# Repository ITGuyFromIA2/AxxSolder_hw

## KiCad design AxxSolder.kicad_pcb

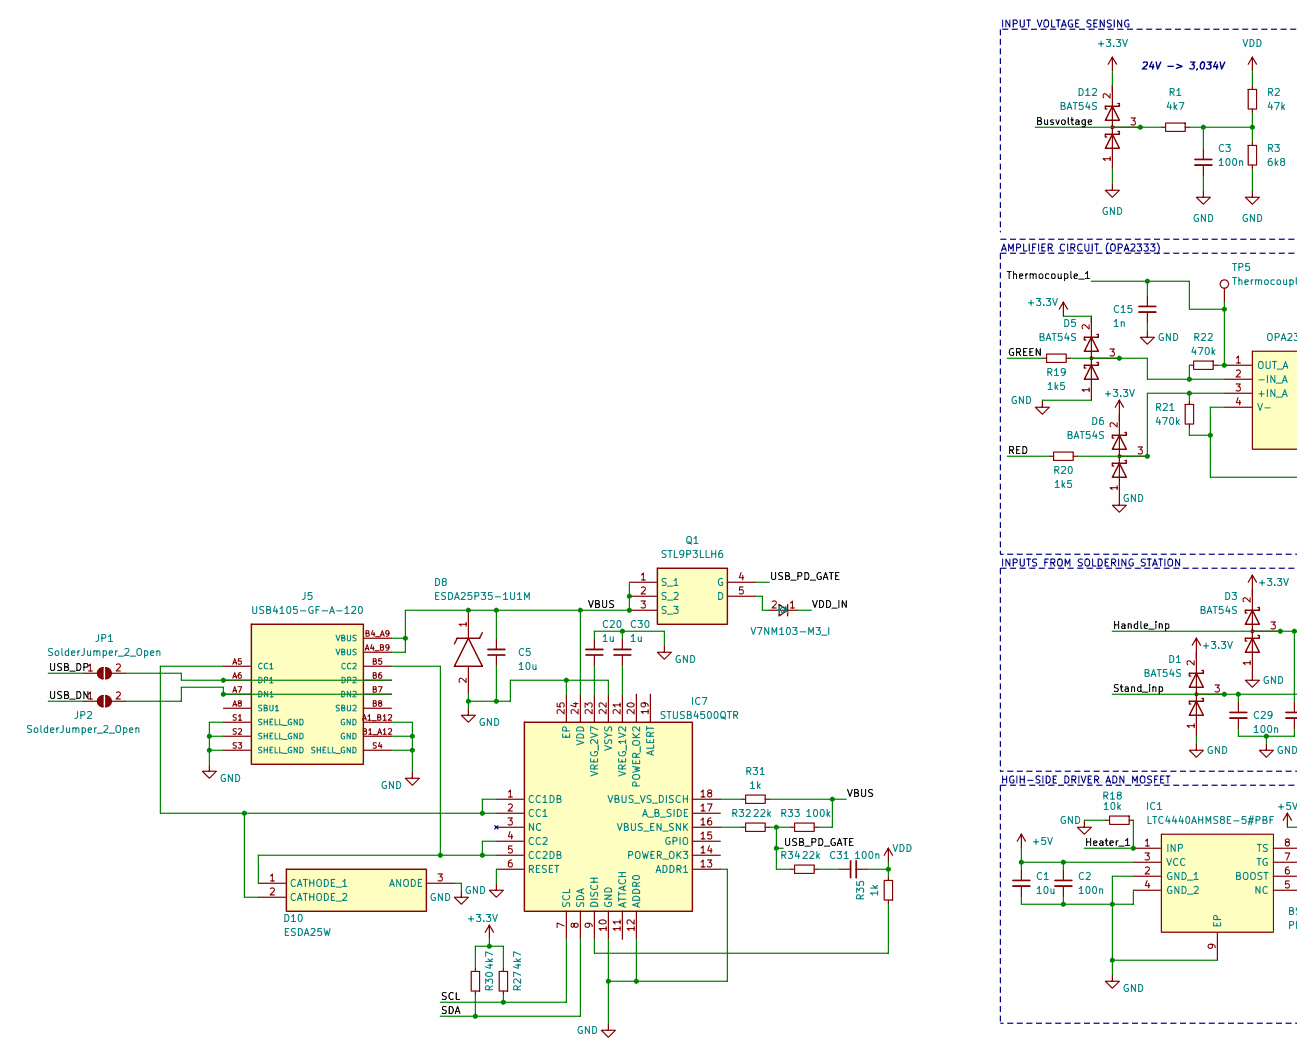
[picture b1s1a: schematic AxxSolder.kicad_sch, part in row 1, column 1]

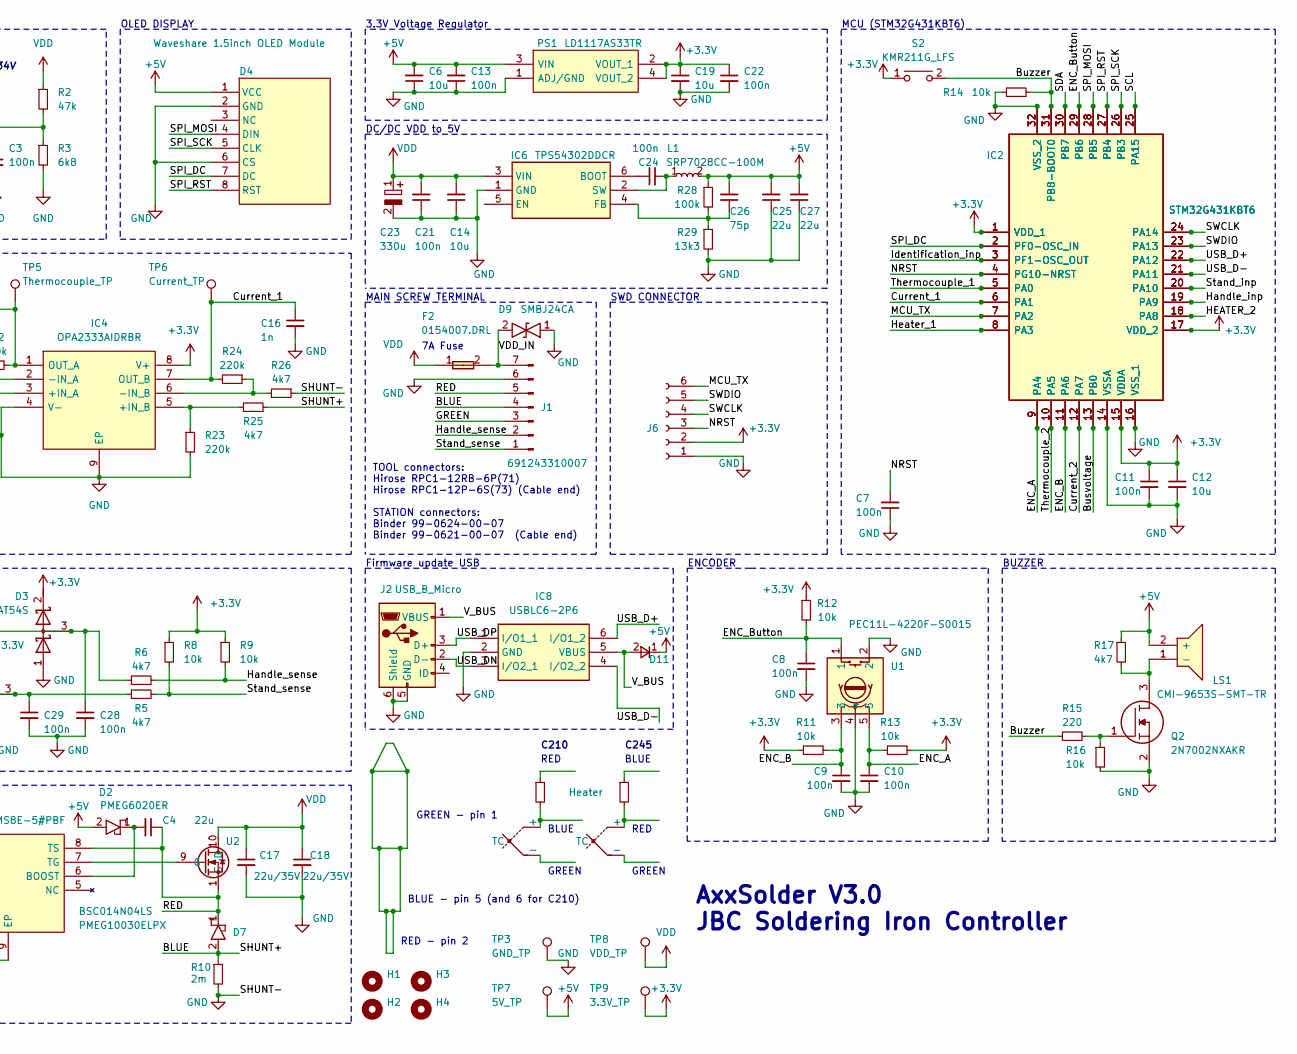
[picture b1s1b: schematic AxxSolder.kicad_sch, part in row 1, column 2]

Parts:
C1, C5, C6, C12, C14, C19: 10u; C_0805_2012Metric; Manufacturer_Part_Number GRM21BR6YA106ME43L
C2, C3, C7, C8, C9, C10, C11, C13, C21, C22, C24, C28, C29, C31: 100n; C_0805_2012Metric; Manufacturer_Part_Number GRM21BR72A104KAC4L
C4, C25, C27: 22u; C_1206_3216Metric; Manufacturer_Part_Number C2012X6S1C226M125AC
C15, C16: 1n; C_0805_2012Metric; Manufacturer_Part_Number GRM2165C1H102JA01D
C17, C18: 22u/35V; C_1206_3216Metric; Manufacturer_Part_Number C3216X5R1V226M160AC
C20, C30: 1u; C_0805_2012Metric; Manufacturer_Part_Number GRM21BC72A105KE01L
C23: 330u; CAPAE1030X1050N; Mouser Part Number 661-EMZR500ARA331MJA
C26: 75p; C_0805_2012Metric; Manufacturer_Part_Number GRM21A5C2E750FW01D
D1, D3, D5, D6, D12: BAT54S; SOT95P230X110-3N; Manufacturer_Part_Number BAT54S
D2: PMEG6020ER; PMEG6020ER115; Mouser Part Number 771-PMEG6020ER-115
D4: Waveshare 1.5inch OLED Module; 1_5inch-rgb-oled-module_asm-1110; Manufacturer_Part_Number N/A
D7: PMEG10030ELPX; SODFL4725X110N; Mouser Part Number 771-PMEG10030ELPX
D8: ESDA25P35-1U1M; ESDA25P351U1M; Mouser Part Number 511-ESDA25P35-1U1M
D9: SMBJ24CA; DIOM5436X261N; Mouser Part Number 576-SMBJ24CA
D10: ESDA25W; SOT65P210X110-3N; Mouser Part Number 511-ESDA25W
D11: 1N5819HW-7-F; SOD3716X145N; Mouser Part Number 621-1N5819HW-F
D13: V7NM103-M3_I; V7NM103M3I; Mouser Part Number 625-V7NM103-M3/I
F2: 0154007.DRL; 0154100DR; Mouser Part Number 576-0154007.DRL
H1, H2, H3, H4: MountingHole; MountingHole_3mm
IC1: LTC4440AHMS8E-5#PBF; SOP65P490X110-9N; Mouser Part Number 584-C4440AHMS8E-5PBF
IC2: STM32G431KBT6; QFP80P900X900X160-32N; Mouser Part Number 511-STM32G431KBT6
IC4: OPA2333AIDRBR; SON65P300X300X100-9N-D; Mouser Part Number 595-OPA2333AIDRBR
IC5: STM32G431KBT6; UFQFPN-32-1EP_5x5mm_P0.5mm_EP3.5x3.5mm; Mouser Part Number 511-STM32G431KBT6
IC6: TPS54302DDCR; SOT95P280X110-6N; Mouser Part Number 595-TPS54302DDCR
IC7: STUSB4500QTR; QFN50P400X400X100-25N-D; Mouser Part Number 511-STUSB4500QTR
IC8: USBLC6-2P6; USBLC62P6; Mouser Part Number 511-USBLC6-2P6
J1: Conn_01x07_Male; 691243310007; Manufacturer_Part_Number 691243310007
J2: USB_B_Micro; GCT_USB3140-30-0230-1-C_REVE1; Manufacturer_Part_Number USB3140-30-0170-0-C
J5: USB4105-GF-A-120; GCT_USB4105-GF-A-120; PARTREV A3
J6: Conn_01x06_Socket; PinSocket_1x06_P2.54mm_Vertical; Manufacturer_Part_Number 61300611821
JP1, JP2: SolderJumper_2_Open; SolderJumper-2_P1.3mm_Open_TrianglePad1.0x1.5mm
L1: SRP7028CC-100M; INDPM7366X300N; Manufacturer_Part_Number SRP7028CC-100M
LS1: CMI-9653S-SMT-TR; CMI9653SSMTTR; Mouser Part Number 490-CMI-9653S-SMT-TR
PS1: LD1117AS33TR; SOT230P700X190-4N; Mouser Part Number 511-LD1117AS33
Q1: STL9P3LLH6; STL20N6F7; Mouser Part Number 511-STL9P3LLH6
Q2: 2N7002NXAKR; SOT95P230X110-3N; Manufacturer_Part_Number 2N7002NXAKR; Mouser Part Number 771-2N7002NXAKR
R1, R5, R6, R17, R25, R26, R27, R30: 4k7; R_0805_2012Metric; Manufacturer_Part_Number ERJ-6ENF4701V
R2: 47k; R_0805_2012Metric; Manufacturer_Part_Number ERJ-6ENF4702V
R3: 6k8; R_0805_2012Metric; Manufacturer_Part_Number ERJ-6ENF6801V
R4: Heater
R7: Heater 2 OHM
R8, R9, R11, R12, R13, R14, R16, R18: 10k; R_0805_2012Metric; Manufacturer_Part_Number ERJ-6ENF1002V
R10: 2m; RESC6432X89N; part_id WSLP25122L500FEA
R15: 220; R_0805_2012Metric; Manufacturer_Part_Number ERJ-6ENF2200V
R19, R20: 1k5; R_0805_2012Metric; Manufacturer_Part_Number ERJ-6ENF1501V
R21, R22: 470k; R_0805_2012Metric; Manufacturer_Part_Number ERJ-6ENF4703V
R23, R24: 220k; R_0805_2012Metric; Manufacturer_Part_Number ERJ-6ENF2203V
R28, R33: 100k; R_0805_2012Metric; Manufacturer_Part_Number ERJ-6ENF1003V
R29: 13k3; R_0805_2012Metric; Manufacturer_Part_Number ERJ-6ENF1332V
R31, R35: 1k; R_0805_2012Metric; Manufacturer_Part_Number ERJ-6ENF1001V
R32, R34: 22k; R_0805_2012Metric; Manufacturer_Part_Number ERJ-6ENF2202V
S2: KMR211G_LFS; KMR_2; Manufacturer_Part_Number KMR211G LFS; Mouser Part Number 611-KMR211G-LFS
TC1, TC2: TC
TP3: GND_TP; TestPoint_THTPad_D1.0mm_Drill0.5mm
TP5: Thermocouple_TP; TestPoint_Pad_D1.0mm
TP6: Current_TP; TestPoint_Pad_D1.0mm
TP7: 5V_TP; TestPoint_THTPad_D1.0mm_Drill0.5mm
TP8: VDD_TP; TestPoint_THTPad_D1.0mm_Drill0.5mm
TP9: 3.3V_TP; TestPoint_THTPad_D1.0mm_Drill0.5mm
U1: PEC11L-4220F-S0015; PEC11L4220FS0015; Mouser Part Number 652-PEC11L4220FS0015
U2: BSC014N04LS; Manufacturer_Part_Number BSC014N04LSATMA1

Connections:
+3.3V: C11.1, C12.1, C19.1, C22.1, D1.2 (K), D3.2 (K), D5.2 (K), D6.2 (K), D12.2 (K), IC2.1 (VDD_1), IC2.15 (VDDA), IC2.17 (VDD_2), IC4.8 (V+), IC5.1 (VDD_1), IC5.15 (VDDA), IC5.17 (VDD_2), J6.2, PS1.2 (VOUT_1), PS1.4 (VOUT_2), R8.1, R9.1, R11.2, R12.1, R13.1, R27.2, R30.2, S2.1, TP9.1
+5V: C1.1, C2.1, C6.2, C13.2, C25.2, C26.2, C27.2, D2.2, D4.1 (VCC), D11.1, IC1.3 (VCC), L1.2, LS1.2 (+), PS1.3 (VIN), R17.1, R28.1, TP7.1
/BLUE: D7.2, J1.4, R10.1, R25.2
/Busvoltage: D12.3 (common), IC2.13 (PB0), IC5.13 (PB0), R1.2
/Buzzer: IC2.31 (PB8-BOOT0), IC5.31 (PB8-BOOT0), R14.2, R15.1, S2.2
/Current_1: C16.1, IC2.6 (PA1), IC4.7 (OUT_B), IC5.6 (PA1), R24.2, TP6.1; also elsewhere on the board
/Current_2: IC2.12 (PA7), IC5.12 (PA7)
/ENC_A: C10.1, IC2.9 (PA4), IC5.9 (PA4), R13.2, U1.5
/ENC_B: C9.1, IC2.11 (PA6), IC5.11 (PA6), R11.1, U1.3
/ENC_Button: C8.1, IC2.29 (PB6), IC5.29 (PB6), R12.2, U1.1
/GREEN: J1.3, R19.1
/HEATER_2: IC2.18 (PA8), IC5.18 (PA8)
/Handle_inp: C28.1, D3.3 (common), IC2.19 (PA9), IC5.19 (PA9), R6.1
/Handle_sense: J1.2, R6.2, R9.2
/Heater_1: IC1.1 (INP), IC2.8 (PA3), IC5.8 (PA3), R18.1
/Identification_inp: IC2.3 (PF1-OSC_OUT), IC5.3 (PF1-OSC_OUT)
/MCU_TX: IC2.7 (PA2), IC5.7 (PA2), J6.6
/NRST: C7.2, IC2.4 (PG10-NRST), IC5.4 (PG10-NRST), J6.3
/RED: C4.1, D7.1, IC1.8 (TS), J1.5, R20.1, U2.1 (S)
/SCL: IC2.25 (PA15), IC5.25 (PA15), IC7.7 (SCL), R27.1
/SDA: IC2.30 (PB7), IC5.30 (PB7), IC7.8 (SDA), R30.1
/SPI_DC: D4.7 (DC), IC2.2 (PF0-OSC_IN), IC5.2 (PF0-OSC_IN)
/SPI_MOSI: D4.4 (DIN), IC2.28 (PB5), IC5.28 (PB5)
/SPI_RST: D4.8 (RST), IC2.27 (PB4), IC5.27 (PB4)
/SPI_SCK: D4.5 (CLK), IC2.26 (PB3), IC5.26 (PB3)
/SWCLK: IC2.24 (PA14), IC5.24 (PA14), J6.4
/SWDIO: IC2.23 (PA13), IC5.23 (PA13), J6.5
/Stand_inp: C29.1, D1.3 (common), IC2.20 (PA10), IC5.20 (PA10), R5.1
/Stand_sense: J1.1, R5.2, R8.2
/Thermocouple_1: C15.1, IC2.5 (PA0), IC4.1 (OUT_A), IC5.5 (PA0), R22.1, TP5.1; also elsewhere on the board
/Thermocouple_2: IC2.10 (PA5), IC5.10 (PA5)
/USB_D+: IC2.22 (PA12), IC5.22 (PA12), IC8.6 (I/O1_2)
/USB_D-: IC2.21 (PA11), IC5.21 (PA11), IC8.4 (I/O2_2)
/USB_DN: IC8.3 (I/O2_1), J2.2 (D-), JP2.1 (A)
/USB_DP: IC8.1 (I/O1_1), J2.3 (D+), JP1.1 (A)
/USB_PD_GATE: Q1.4 (G), R32.2, R33.1, R34.1
/VBUS: C5.2, D8.1 (K), IC7.24 (VDD), J5.A4_B9 (VBUS), J5.B4_A9 (VBUS), Q1.1 (S_1), Q1.2 (S_2), Q1.3 (S_3), R31.2, R33.2
/VDD_IN: D9.2, D13.1 (K), F2.2, J1.7
/V_BUS: D11.2, IC8.5 (VBUS), J2.1 (VBUS)
GND: C1.2, C2.2, C3.2, C5.1, C6.1, C7.1, C8.2, C9.2, C10.2, C11.2, C12.2, C13.1, C14.1, C15.2, C16.2, C17.2, C18.2, C19.2, C20.2, C21.1, C22.2, C23.2, C25.1, C27.1, C28.2, C29.2, C30.2, D1.1 (A), D3.1 (A), D4.2 (GND), D4.6 (CS), D5.1 (A), D6.1 (A), D8.2 (A), D9.1, D10.3 (ANODE), D12.1 (A), IC1.2 (GND_1), IC1.4 (GND_2), IC1.9 (EP), IC2.14 (VSSA), IC2.16 (VSS_1), IC2.32 (VSS_2), IC4.4 (V-), IC4.9 (EP), IC5.14 (VSSA), IC5.16 (VSS_1), IC5.32 (VSS_2), IC6.1 (GND), IC7.6 (RESET), IC7.10 (GND), IC7.12 (ADDR0), IC7.13 (ADDR1), IC7.22 (VSYS), IC7.25 (EP), IC8.2 (GND), J1.6, J2.5 (GND), J2.6 (Shield), J5.A1_B12 (GND), J5.B1_A12 (GND), J5.S1 (SHELL_GND), J5.S2 (SHELL_GND), J5.S3 (SHELL_GND), J5.S4 (SHELL_GND), J6.1, PS1.1 (ADJ/GND), Q2.2, R3.2, R10.2, R14.1, R16.2, R18.2, R21.2, R23.2, R26.1, R29.2, TP3.1, U1.2, U1.4
unnamed: C3.1, R1.1, R2.2, R3.1
unnamed: C31.1, R34.2
unnamed: D5.3 (common), IC4.2 (-IN_A), R19.2, R22.2
unnamed: D6.3 (common), IC4.3 (+IN_A), R20.2, R21.1
unnamed: D10.1 (CATHODE_1), IC7.4 (CC2), IC7.5 (CC2DB), J5.B5 (CC2)
unnamed: D10.2 (CATHODE_2), IC7.1 (CC1DB), IC7.2 (CC1), J5.A5 (CC1)
unnamed: D13.2 (A), Q1.5 (D)
unnamed: C4.2, D2.1, IC1.6 (BOOST)
unnamed: IC1.7 (TG), U2.9 (G)
unnamed: IC4.5 (+IN_B), R23.1, R25.1
unnamed: IC4.6 (-IN_B), R24.1, R26.2
unnamed: C24.1, IC6.6 (BOOT)
unnamed: C26.1, IC6.4 (FB), R28.2, R29.1
unnamed: C24.2, IC6.2 (SW), L1.1
unnamed: IC7.9 (DISCH), R35.1
unnamed: IC7.16 (VBUS_EN_SNK), R32.1
unnamed: IC7.18 (VBUS_VS_DISCH), R31.1
unnamed: C30.1, IC7.21 (VREG_1V2)
unnamed: C20.1, IC7.23 (VREG_2V7)
unnamed: J5.A7 (DN1), J5.B7 (DN2), JP2.2 (B)
unnamed: J5.A6 (DP1), J5.B6 (DP2), JP1.2 (B)
unnamed: LS1.1 (-), Q2.3, R17.2
unnamed: Q2.1, R15.2, R16.1
unnamed: R4.2, TC1.1 (+)
unnamed: R7.2, TC2.1 (+)
VDD: C14.2, C17.1, C18.1, C21.2, C23.1, C31.2, F2.1, IC6.3 (VIN), R2.1, R35.2, TP8.1, U2.10 (D)

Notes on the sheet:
7A Fuse
C210
Firmware update USB
MCU (STM32G431KBT6)
C245
GREEN - pin 1
MAIN SCREW TERMINAL
AMPLIFIER CIRCUIT (OPA2333)
24V -> 3,034V
INPUT VOLTAGE SENSING
ENCODER
SWD CONNECTOR
BLUE
BLUE - pin 5 (and 6 for C210)
GREEN
RED
BUZZER
DC/DC VDD to 5V
AxxSolder V3.0 JBC Soldering Iron Controller
TOOL connectors: Hirose RPC1-12RB-6P(71) Hirose RPC1-12P-6S(73) (Cable end) STATION connectors: Binder 99-0624-00-07 Binder 99-0621-00-07 (Cable end)
INPUTS FROM SOLDERING STATION
HGIH-SIDE DRIVER ADN MOSFET
RED - pin 2
RED
3.3V Voltage Regulator
OLED DISPLAY

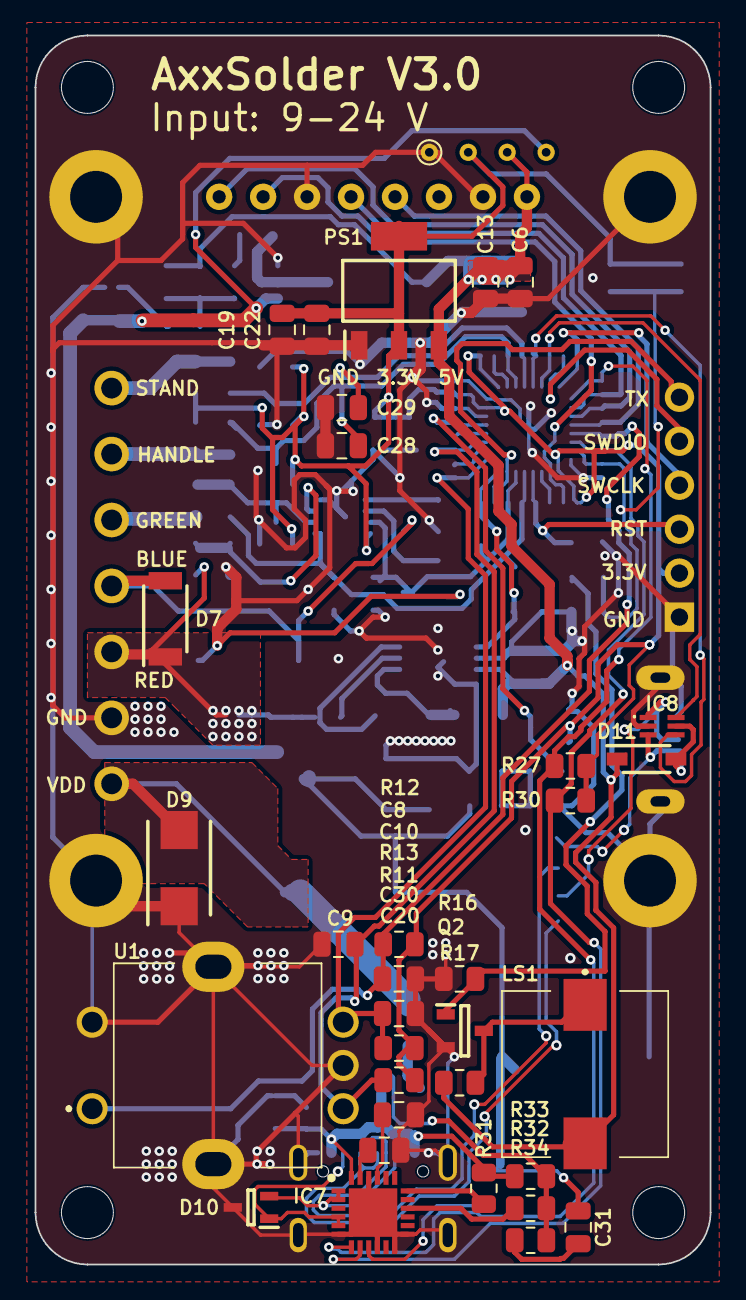
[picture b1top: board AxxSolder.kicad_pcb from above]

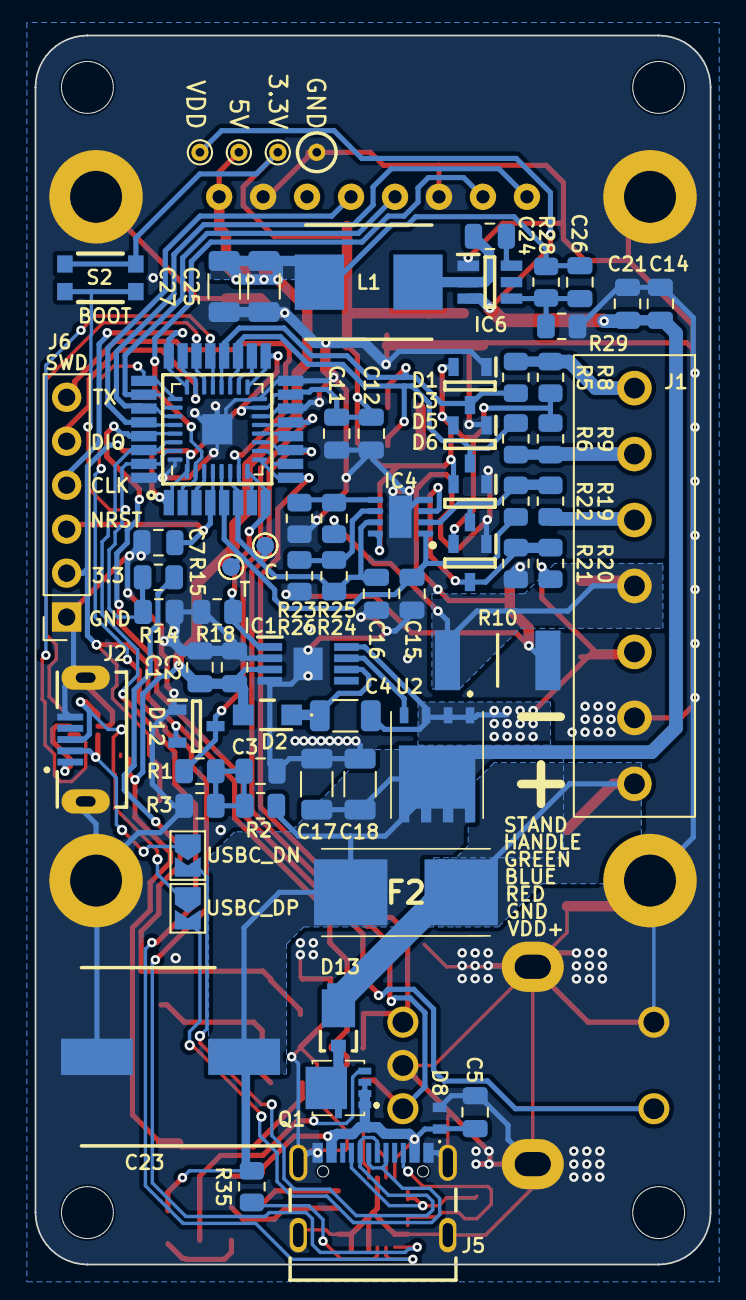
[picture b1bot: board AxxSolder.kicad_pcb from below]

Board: 2 copper layers, 39.0 x 71.0 mm, 111 parts (73 on the bottom side), 64 nets.

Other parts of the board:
TP5#2: Thermocouple_TP; TestPoint_Pad_D1.0mm
TP6#2: Current_TP; TestPoint_Pad_D1.0mm

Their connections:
/Current_1: TP6#2.1; also elsewhere on the board
/Thermocouple_1: TP5#2.1; also elsewhere on the board

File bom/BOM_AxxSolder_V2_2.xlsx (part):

AxxSolder V2.2 | Prises as per 2023-10-03 |  | Parts for AxxSolder Station only
 |  |  | Parts for AxxSolder Poratble only
Part | Value | Device | Footprint | # in design | Price / component | Price / unit |  |  | Datasheet | Manufacturer_Part_Number | Mouser Part Number
C1, C6, C12, C14, C19 | 10u | Device:C_Small | Capacitor_SMD:C_0805_2012Metric | 5 | 0.32 | 1.6 | https://www.mouser.se/ProductDetail/Murata-Electronics/GRM21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 | https://www.mouser.com/ProductDetail/Murata-Electronics/GRM2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 | ~
C2, C3, C5, C7, C8, C9, C10, C11, C13, C20, C21, C22, C24, C28, C29 | 100n | Device:C_Small | Capacitor_SMD:C_0805_2012Metric | 15 | 9.2999999999999999E-2 | 1.395 | https://www.mouser.se/ProductDetail/KYOCERA-AVX/KGM21NR71H10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 | https://www.mouser.com/ProductDetail/KYOCERA-AVX/KGM21NR71H1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 | ~
C4, C25, C27 | 22u | Device:C_Small | Capacitor_SMD:C_1206_3216Metric | 3 | 0.54 | 1.62 | https://www.mouser.se/ProductDetail/TDK/C2012X6S1C226M125AC?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 | https://www.mouser.com/ProductDetail/TDK/C2012X6S1C226M125AC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
C17, C18 | 22u/35V | Device:C_Small | Capacitor_SMD:C_0805_2012Metric | 2 | 0.88 | 1.76 | https://www.mouser.se/ProductDetail/TDK/C3216X5R1V226M160AC?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 | https://www.mouser.com/ProductDetail/TDK/C3216X5R1V226M160AC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
C15, C16 | 1n | Device:C_Small | Capacitor_SMD:C_0805_2012Metric | 2 | 9.2999999999999999E-2 | 0.186 | https://www.mouser.se/ProductDetail/KYOCERA-AVX/KGM21NR71H10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 | https://www.mouser.com/ProductDetail/KYOCERA-AVX/KGM21NR71H1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 | ~
C23 | 330u | EMZR500ARA331MJA0G:EMZR500ARA331MJA0G | EMZR500ARA331MJA0G:CAPAE1030X1050N | 1 | 1.1599999999999999 | 1.1599999999999999 | https://www.mouser.se/ProductDetail/Chemi-Con/EMZR500ARA331M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 | https://www.mouser.com/ProductDetail/Chemi-Con/EMZR500ARA331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 | https://ru.mouser.com/datasheet/2/420/United-Chemi-Con-776012.pdf | EMZR500ARA331MJA0G | 661-EMZR500ARA331MJA
C26 | 75p | Device:C_Small | Capacitor_SMD:C_0805_2012Metric | 1 | 0.15 | 0.15 | https://www.mouser.se/ProductDetail/KYOCERA-AVX/08051A750JAT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 | https://www.mouser.com/ProductDetail/KYOCERA-AVX/08051A750JA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 |  | 08051A750JAT2A
D1, D3, D5, D6, D12 | BAT54S | Device:D_Schottky_Dual_Series_AKC | BAT54S,215:SOT95P230X110-3N | 5 | 0.26 | 1.3 | https://www.mouser.se/ProductDetail/Diotec-Semiconductor/BAT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 | https://www.mouser.com/ProductDetail/Diotec-Semiconductor/BA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 | ~
D2 | PMEG6020ER | PMEG6020ER_115:PMEG6020ER,115 | PMEG6020ER,115:PMEG6020ER115 | 1 | 0.41899999999999998 | 0.41899999999999998 | https://www.mouser.se/ProductDetail/Nexperia/PMEG6020ER115?q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 | https://www.mouser.com/ProductDetail/Nexperia/PMEG6020ER115?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 | https://assets.nexperia.com/documents/data-sheet/PMEG6020ER.pdf | PMEG6020ER,115 | 771-PMEG6020ER-115
D4 | Waveshare 1.5inch OLED Module | 1_5inch-rgb-oled-module_asm-1110:1_5inch-rgb-oled-module_asm-1110 | 1_5inch-rgb-oled-module_asm-1110:1_5inch-rgb-oled-module_asm-1110 | 1 | 12.9 | 12.9 | https://www.welectron.com/Waveshare-13992-15inch-OLED-Module_1 | https://www.welectron.com/Waveshare-13992-15inch-OLED-Module_1
D7 | PMEG10030ELPX | PMEG10030ELPX:PMEG10030ELPX | PMEG10030ELPX:SODFL4725X110N | 1 | 0.44600000000000001 | 0.44600000000000001 | https://www.mouser.se/ProductDetail/Nexperia/PMEG10030ELPX?q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 | https://www.mouser.com/ProductDetail/Nexperia/PMEG10030ELPX?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 | https://assets.nexperia.com/documents/data-sheet/PMEG10030ELP.pdf | PMEG10030ELPX | 771-PMEG10030ELPX
D9 | SMBJ24CA | SMBJ24CA:SMBJ24CA | DIOM5436X261N | 1 | 0.34399999999999997 | 0.34399999999999997 | https://www.mouser.se/ProductDetail/Littelfuse/SMBJ24CA?qs=J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 | https://www.mouser.com/ProductDetail/Littelfuse/SMBJ24CA?qs=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 | https://www.mouser.se/datasheet/2/240/media-3319099.pdf | SMBJ24CA | 576-SMBJ24CA
F1 | 10A Fuse | Device:Fuse | 3557-2:3557-2 | 1 | 1.1000000000000001 | 1.1000000000000001 | https://www.mouser.se/ProductDetail/Keystone-Electronics/355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 | https://www.mouser.com/ProductDetail/Keystone-Electronics/35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 | ~
IC1 | LTC4440AHMS8E-5#PBF | LTC4440AHMS8E-5#PBF:LTC4440AHMS8E-5#PBF | LTC4440AHMS8E-5#PBF:SOP65P490X110-9N | 1 | 5.72 | 5.72 | https://www.mouser.se/ProductDetail/Analog-Devices/LTC4440AH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 | https://www.mouser.com/ProductDetail/Analog-Devices/LTC4440A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 | https://www.arrow.com/en/products/ltc4440ahms8e-5pbf/analog-devices | LTC4440AHMS8E-5#PBF | 584-C4440AHMS8E-5PBF
IC2 | STM32G431KBT6 | STM32G431KBT6:STM32G431KBT6 | STM32G431KBT6:QFP80P900X900X160-32N | 1 | 6.45 | 6.45 | https://www.mouser.se/ProductDetail/STMicroelectronics/STM32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 | https://www.mouser.com/ProductDetail/STMicroelectronics/STM3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 | https://www.st.com/resource/en/datasheet/stm32g431kb.pdf | STM32G431KBT6 | 511-STM32G431KBT6
L1 | SRP7028CC-100M | SRP7028CC-100M:SRP7028CC-100M | INDPM7366X300N | 1 | 0.75 | 0.75 | https://www.mouser.se/ProductDetail/Bourns/SRP7028CC-100M?qs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 | https://www.mouser.com/ProductDetail/Bourns/SRP7028CC-100M?q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 | https://www.bourns.com/docs/Product-Datasheets/SRP7028CC.pdf | SRP7028CC-100M | 652-SRP7028CC-100M
IC3 | TMP236AQDBZRQ1 | TMP236AQDBZRQ1:TMP236AQDBZRQ1 | TMP236AQDBZRQ1:SOT95P237X112-3N | 1 | 0.54900000000000004 | 0.54900000000000004 | https://www.mouser.se/ProductDetail/Texas-Instruments/TMP236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 | https://www.mouser.com/ProductDetail/Texas-Instruments/TMP23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 | https://www.ti.com/lit/gpn/TMP236-Q1 | TMP236AQDBZRQ1 | 595-TMP236AQDBZRQ1
IC4 | OPA2333AIDRBR | OPA2333AIDRBR:OPA2333AIDRBR | OPA2333AIDRBR:SON65P300X300X100-9N-D | 1 | 3.78 | 3.78 | https://www.mouser.se/ProductDetail/Texas-Instruments/OPA233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 | https://www.mouser.com/ProductDetail/Texas-Instruments/OPA23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 | https://www.ti.com/lit/ds/symlink/opa2333.pdf?ts=16069820250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 | OPA2333AIDRBR | 595-OPA2333AIDRBR
J1 | Conn_01x07_Male | Connector:Conn_01x07_Male | 691243310007:691243310007 | 1 | 2.99 | 2.99 | https://www.mouser.se/ProductDetail/Wurth-Elektronik/6912433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 | https://www.mouser.com/ProductDetail/Wurth-Elektronik/691243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 | ~
J4 | Conn_01x07_Male | Connector:Conn_01x07_Male | Connector_PinSocket_2.54mm:PinSocket_1x07_P2.54mm_Vertical | 1 | 1.5 | 1.5 | https://www.mouser.se/ProductDetail/TE-Connectivity/5-534237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 | https://www.mouser.com/ProductDetail/TE-Connectivity/5-53423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 | ~
LS1 | CMI-9653S-SMT-TR | CMI-9653S-SMT-TR:CMI-9653S-SMT-TR | CMI-9653S-SMT-TR:CMI9653SSMTTR | 1 | 2.71 | 2.71 | https://www.mouser.se/ProductDetail/CUI-Devices/CMI-9653S-SM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 | https://www.mouser.com/ProductDetail/CUI-Devices/CMI-9653S-S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 | https://componentsearchengine.com/Datasheets/1/CMI-9653S-SMT-TR.pdf | CMI-9653S-SMT-TR | 490-CMI-9653S-SMT-TR
PS1 | LD1117AS33TR | LD1117AS33TR:LD1117AS33TR | SOT230P700X190-4N | 1 | 0.83699999999999997 | 0.83699999999999997 | https://www.mouser.se/ProductDetail/STMicroelectronics/LD111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 | https://www.mouser.com/ProductDetail/STMicroelectronics/LD11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 | https://4donline.ihs.com/images/VipMasterIC/IC/SGST/SGSTS493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 | LD1117AS33TR | 511-LD1117AS33
IC6 | TPS54302DDCR | TPS54302DDCR:TPS54302DDCR | SOT95P280X110-6N | 1 | 1.84 | 1.84 | https://www.mouser.se/ProductDetail/Texas-Instruments/TPS543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 | https://www.mouser.com/ProductDetail/Texas-Instruments/TPS54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 | https://www.ti.com/general/docs/suppproductinfo.tsp?distId=2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 | TPS54302DDCT
Q2 | 2N7002NXAKR | 2N7002NXAKR:2N7002NXAKR | 2N7002NXAKR:SOT95P230X110-3N | 1 | 0.17699999999999999 | 0.17699999999999999 | https://www.mouser.se/ProductDetail/Nexperia/2N7002NXAKR?qs=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 | https://www.mouser.com/ProductDetail/Nexperia/2N7002NXAKR?qs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 | https://assets.nexperia.com/documents/data-sheet/2N7002NXAK.pdf | 2N7002NXAKR | 771-2N7002NXAKR
R1, R5, R6, R17, R25, R26 | 4k7 | Device:R_Small | Resistor_SMD:R_0805_2012Metric | 6 | 0.36299999999999999 | 2.1779999999999999 | https://www.mouser.se/ProductDetail/Panasonic/ERJ-HP6D4701V?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 | https://www.mouser.com/ProductDetail/Panasonic/ERJ-HP6D4701V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 | ~
R2 | 47k | Device:R_Small | Resistor_SMD:R_0805_2012Metric | 1 | 0.186 | 0.186 | https://www.mouser.se/ProductDetail/Panasonic/ERJ-P06F4702V?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 | https://www.mouser.com/ProductDetail/Panasonic/ERJ-P06F4702V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 | ~
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
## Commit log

2023-09-12 Add "KiCad.gitignore"
2023-10-03 Add AxxSolder V2.0 BOM with cost
2023-10-03 update BOM_AxxSolder_V2_0-xlsx with cleaner links
2023-10-03 Add BOM_AxxSolder_V2_0.pdf
2023-10-06 Change to new, more cost effective VCC->5V DC/DC solution, update to AxxSolder V2.1
2023-10-06 Clean and structure schematic and update to AxxSolder V2.1
2023-10-06 Clean and structure PCB Layout and update to AxxSolder V2.1
2023-10-07 Change silkscreen to Input: 9-24V and optimize board layout
2023-10-07 Update PCB_3D.jpg with new version
2023-10-08 Update schematic to reflect new naming of inputs, Stand_inp and Handle_inp
2023-10-09 Add screws and fuse to BOM
2023-10-09 Update schematic with proper connections
2023-10-10 Add .lck files
2023-10-10 Add files with ending with # to KiCad.gitignore
2023-10-10 Change capacitor to higher voltage rating
2023-10-10 Add component library
2023-10-10 Update connectors in BOM
2023-10-10 update interactive BOM
2023-10-14 Fix output voltage from DC/DC by switching values of R28 and R27. Also change value of C24
2023-10-15 Improve PCB layout slightly and update gerbers with cu-filled GND layer
2023-10-16 Update BOM with C25 to be a 0805 Capacitor
2023-10-18 Update PCB design to V2.2 - correct fault in 5V DC/DC and change the VDD tVS diode to a 600W instead of 1.5kW and small PCB improvements
2023-10-18 Update BOM
2023-10-21 Update schematic to have show correct intenrnal connestions of JBC cartridges according to https://www.eevblog.com/forum/projects/axxsolder-jbc-soldering-controller/msg5124267/#msg5124267
2023-11-19 remove PCB from main repository
2023-11-19 Revert "remove PCB from main repository"
    This reverts commit 601f9d739a9a2e6bb7cbf2039fa2e6ec6f202c83.
2023-11-28 import USB-PD hardware from AxxSolder
